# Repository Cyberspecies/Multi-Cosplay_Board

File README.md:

# Multi-Cosplay_Board
The board should be capable of driving nearly any electrically active cosplay suit or project including props. The system must also remain cheap and affordable with inter and extrapolation capabilities allowing it to be reducibly complex and still function. The software must also be easy to configure and implement (as this is a platform supported by [ARCOS](https://github.com/XCR1793/ARCOS)).

## Features
* Movement detection via the [ICM-20948](https://invensense.tdk.com/products/motion-tracking/9-axis/icm-20948/), which allows users to track their linear and angular accelerations for animations that require shaking, turning or any other activity requiring user displacement.
* Designed with a small form-factor which users can take advantage of by hiding the circuit board in tight spaces to not get it in the way of aesthetics.
* Fast processing core being the [ESP32-S3 Modules](https://www.espressif.com/en/products/socs/esp32) contains a 280Mhz dual core processor allowing partial asynchronous parallel calculations required for detecting user input and computing sequences at the same time whilst remaining as affordable as possible.

## Roadmap
* Milestone: Nothing Yet
* Work In Progress: Ideation & PCB Component Placement & Feature Integration
* Planned: MCB Version 1
* Planned: ARCOS Integration

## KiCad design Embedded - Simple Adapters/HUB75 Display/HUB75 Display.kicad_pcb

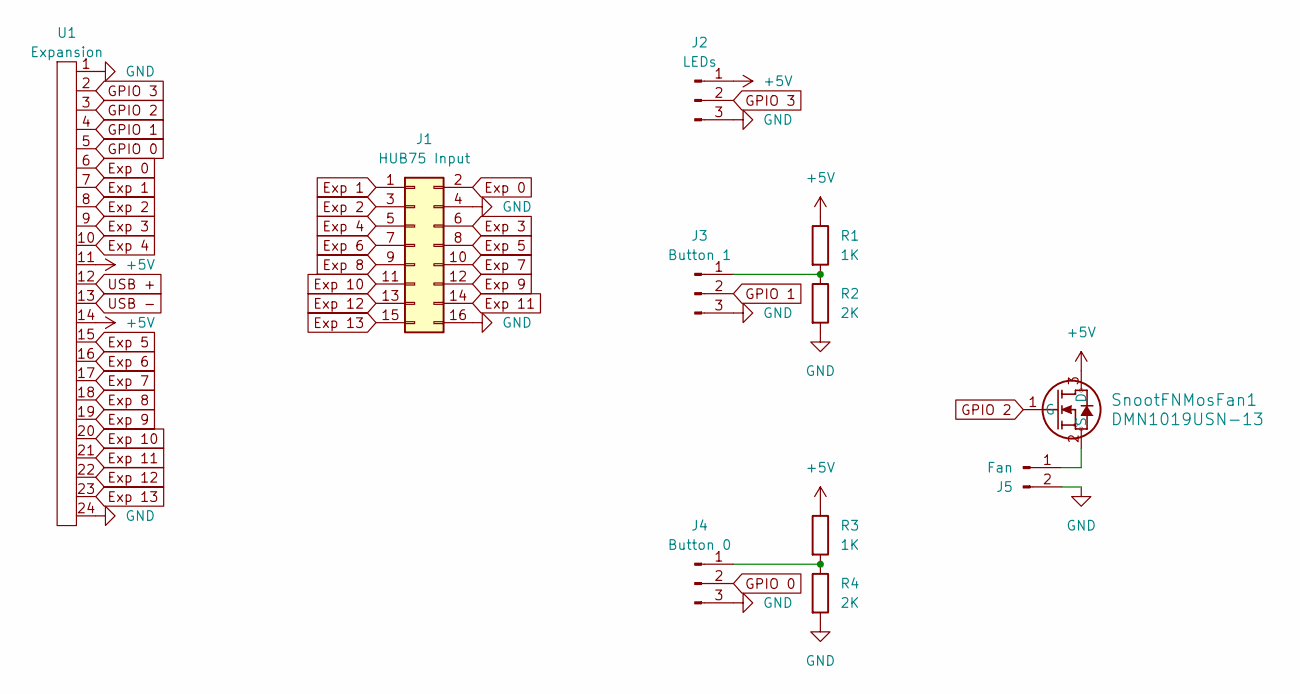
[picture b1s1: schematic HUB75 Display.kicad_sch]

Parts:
J1: HUB75 Input; PinHeader_2x08_P2.54mm_Vertical
J2: LEDs; PinHeader_1x03_P2.54mm_Vertical
J3: Button 1; PinHeader_1x03_P2.54mm_Vertical
J4: Button 0; PinHeader_1x03_P2.54mm_Vertical
J5: Fan; PinHeader_1x02_P2.54mm_Vertical
R1, R3: 1K; R_0603_1608Metric_Pad0.98x0.95mm_HandSolder
R2, R4: 2K; R_0603_1608Metric_Pad0.98x0.95mm_HandSolder
SnootFNMosFan1: DMN1019USN-13; SOT-23-3
U1: Expansion; FFC Aliexpress 0.5mm 24P

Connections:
+5V: J2.1, R1.1, R3.1, SnootFNMosFan1.3 (D), U1.11, U1.14
Exp 0: J1.2, U1.6
Exp 1: J1.1, U1.7
Exp 2: J1.3, U1.8
Exp 3: J1.6, U1.9
Exp 4: J1.5, U1.10
Exp 5: J1.8, U1.15
Exp 6: J1.7, U1.16
Exp 7: J1.10, U1.17
Exp 8: J1.9, U1.18
Exp 9: J1.12, U1.19
Exp 10: J1.11, U1.20
Exp 11: J1.14, U1.21
Exp 12: J1.13, U1.22
Exp 13: J1.15, U1.23
GND: J1.4, J1.16, J2.3, J3.3, J4.3, J5.2, R2.2, R4.2, U1.1, U1.24
GPIO 0: J4.2, U1.5
GPIO 1: J3.2, U1.4
GPIO 2: SnootFNMosFan1.1 (G), U1.3
GPIO 3: J2.2, U1.2
unnamed: J3.1, R1.2, R2.1
unnamed: J4.1, R3.2, R4.1
unnamed: J5.1, SnootFNMosFan1.2 (S)
USB +: U1.12
USB -: U1.13

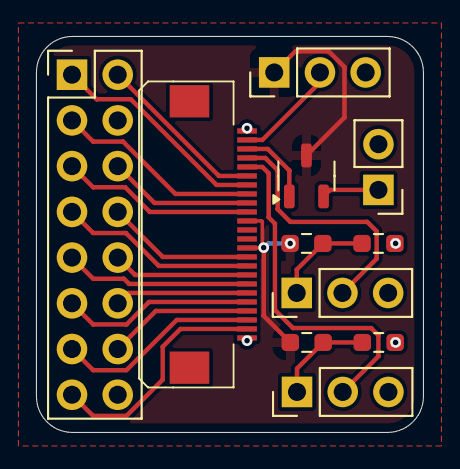
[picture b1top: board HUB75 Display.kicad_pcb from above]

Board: 2 copper layers, 21.5 x 22.0 mm, 11 parts (0 on the bottom side), 23 nets.

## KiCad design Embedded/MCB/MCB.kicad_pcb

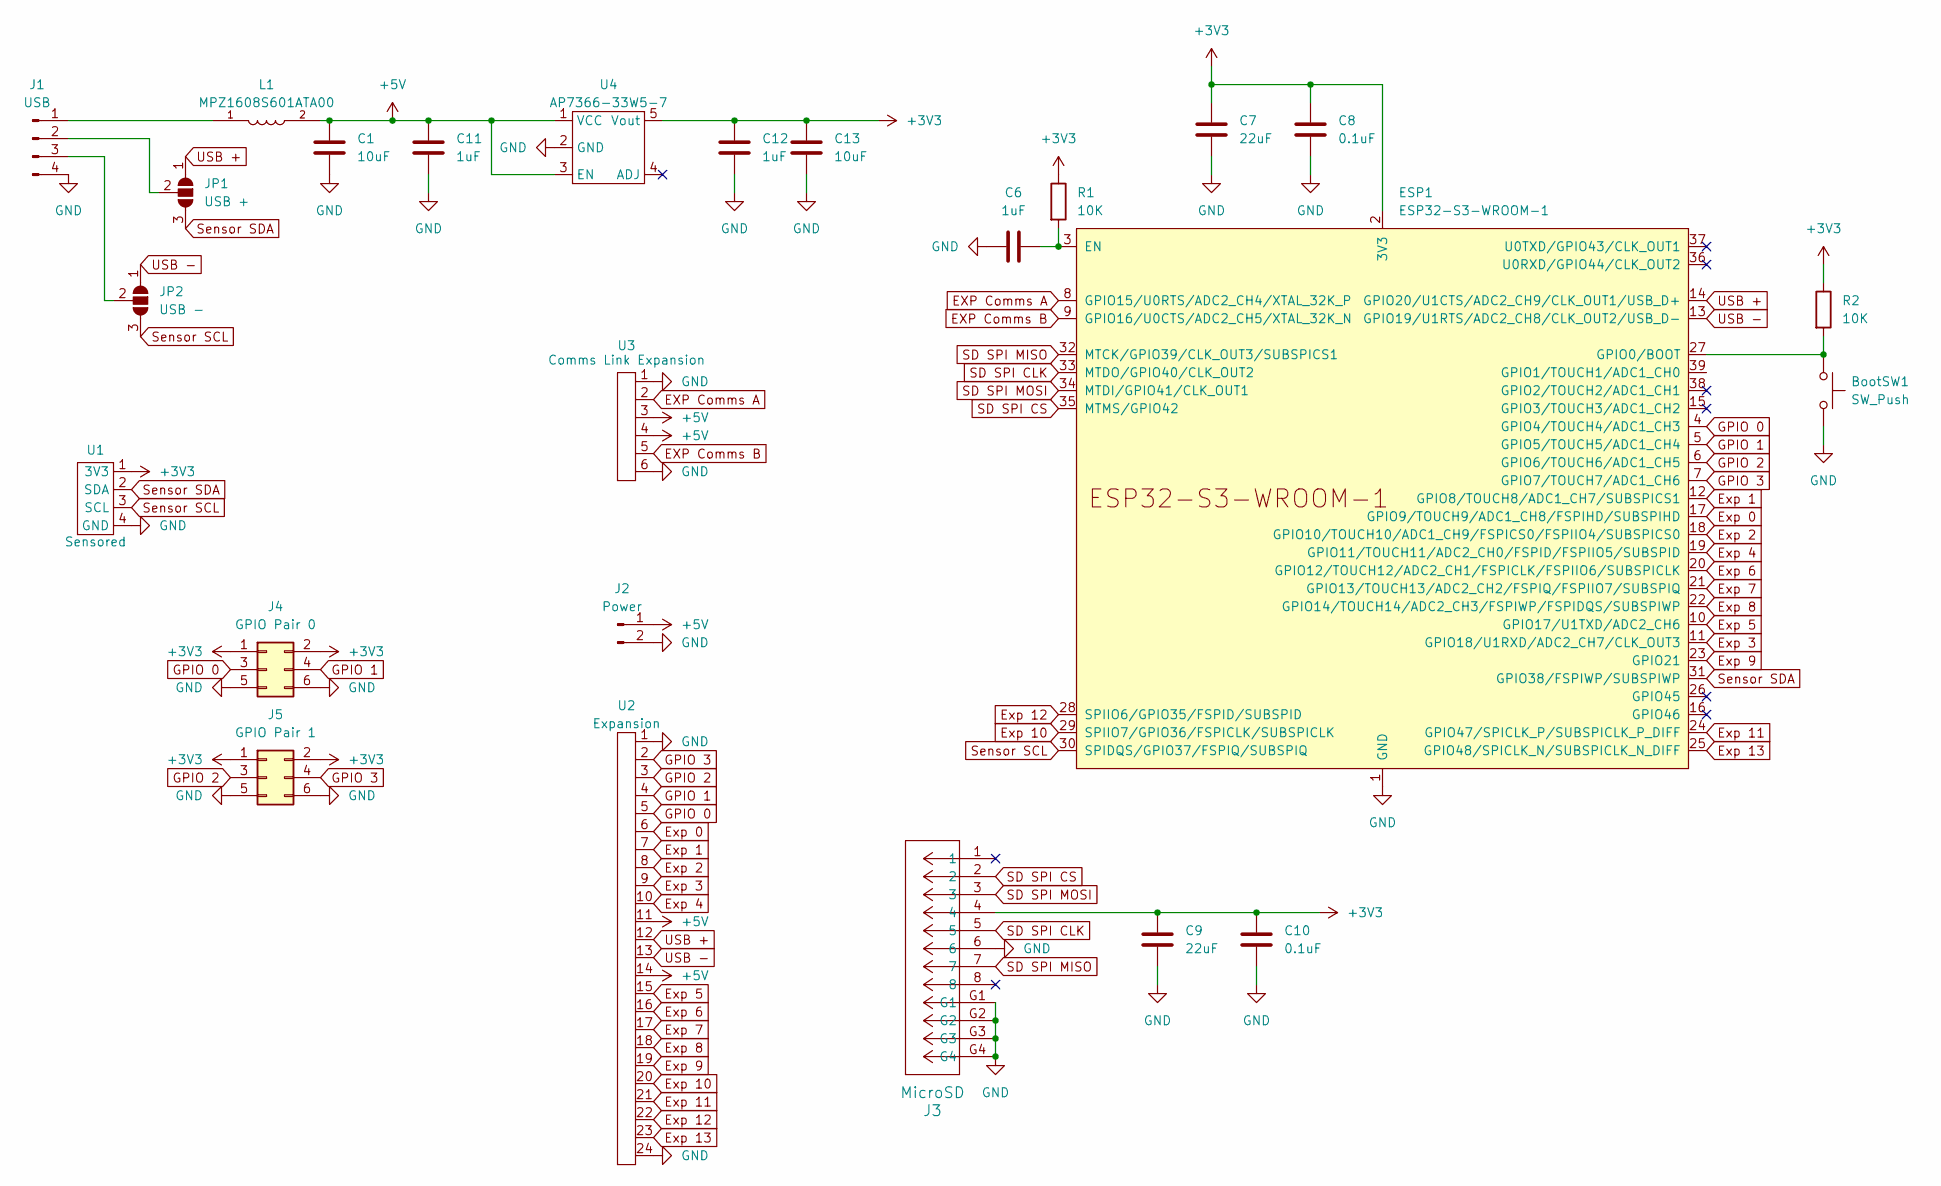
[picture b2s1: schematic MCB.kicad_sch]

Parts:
BootSW1: SW_Push; Button-R-667843
C1, C13: 10uF; C_0603_1608Metric
C6: 1uF; C_0603_1608Metric
C7, C9: 22uF; C_0603_1608Metric_Pad1.08x0.95mm_HandSolder
C8, C10: 0.1uF; C_0603_1608Metric_Pad1.08x0.95mm_HandSolder
C11, C12: 1uF; R_0603_1608Metric
ESP1: ESP32-S3-WROOM-1; ESP32-S3-WROOM-1U
J1: USB; Hirose_DF13-04P-1.25DS_1x04_P1.25mm_Horizontal
J2: Power; Hirose_DF13-02P-1.25DS_1x02_P1.25mm_Horizontal
J3: MicroSD; CONN12_47309-2651_MOL
J4: GPIO Pair 0; PinHeader_2x03_P2.54mm_Vertical
J5: GPIO Pair 1; PinHeader_2x03_P2.54mm_Vertical
JP1: USB +; SolderJumper-3_P1.3mm_Open_RoundedPad1.0x1.5mm
JP2: USB -; SolderJumper-3_P1.3mm_Open_RoundedPad1.0x1.5mm
L1: MPZ1608S601ATA00; INDC1608X95N
R1, R2: 10K; R_0603_1608Metric
U1: Sensored
U2: Expansion; FFC Aliexpress 0.5mm 24P
U3: Comms Link Expansion; FFC Aliexpress 0.5mm 6P
U4: AP7366-33W5-7; AP7366

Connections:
+3V3: C7.1, C8.1, C9.1, C10.1, C12.1, C13.1, ESP1.2 (3V3), J3.4, J4.1, J4.2, J5.1, J5.2, R1.1, R2.1, U1.1 (3V3), U4.5 (Vout)
+5V: C1.1, C11.1, J2.1, L1.2, U2.11, U2.14, U3.3, U3.4, U4.1 (VCC), U4.3 (EN)
EXP Comms A: ESP1.8 (GPIO15/U0RTS/ADC2_CH4/XTAL_32K_P), U3.2
EXP Comms B: ESP1.9 (GPIO16/U0CTS/ADC2_CH5/XTAL_32K_N), U3.5
Exp 0: ESP1.17 (GPIO9/TOUCH9/ADC1_CH8/FSPIHD/SUBSPIHD), U2.6
Exp 1: ESP1.12 (GPIO8/TOUCH8/ADC1_CH7/SUBSPICS1), U2.7
Exp 2: ESP1.18 (GPIO10/TOUCH10/ADC1_CH9/FSPICS0/FSPIIO4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), U2.8
Exp 3: ESP1.11 (GPIO18/U1RXD/ADC2_CH7/CLK_OUT3), U2.9
Exp 4: ESP1.19 (GPIO11/TOUCH11/ADC2_CH0/FSPID/FSPIIO5/S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), U2.10
Exp 5: ESP1.10 (GPIO17/U1TXD/ADC2_CH6), U2.15
Exp 6: ESP1.20 (GPIO12/TOUCH12/ADC2_CH1/FSPICLK/FSPIIO6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), U2.16
Exp 7: ESP1.21 (GPIO13/TOUCH13/ADC2_CH2/FSPIQ/FSPIIO7/S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), U2.17
Exp 8: ESP1.22 (GPIO14/TOUCH14/ADC2_CH3/FSPIWP/FSPIDQS/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), U2.18
Exp 9: ESP1.23 (GPIO21), U2.19
Exp 10: ESP1.29 (SPIIO7/GPIO36/FSPICLK/SUBSPICLK), U2.20
Exp 11: ESP1.24 (GPIO47/SPICLK_P/SUBSPICLK_P_DIFF), U2.21
Exp 12: ESP1.28 (SPIIO6/GPIO35/FSPID/SUBSPID), U2.22
Exp 13: ESP1.25 (GPIO48/SPICLK_N/SUBSPICLK_N_DIFF), U2.23
GND: BootSW1.2, C1.2, C6.1, C7.2, C8.2, C9.2, C10.2, C11.2, C12.2, C13.2, ESP1.1 (GND), ESP1.40 (GND), ESP1.41 (GND), J1.4, J2.2, J3.6, J3.G1, J3.G2, J3.G3, J3.G4, J4.5, J4.6, J5.5, J5.6, U1.4 (GND), U2.1, U2.24, U3.1, U3.6, U4.2 (GND)
GPIO 0: ESP1.4 (GPIO4/TOUCH4/ADC1_CH3), J4.3, U2.5
GPIO 1: ESP1.5 (GPIO5/TOUCH5/ADC1_CH4), J4.4, U2.4
GPIO 2: ESP1.6 (GPIO6/TOUCH6/ADC1_CH5), J5.3, U2.3
GPIO 3: ESP1.7 (GPIO7/TOUCH7/ADC1_CH6), J5.4, U2.2
unnamed: C6.2, ESP1.3 (EN), R1.2
unnamed: BootSW1.1, ESP1.27 (GPIO0/BOOT), R2.2
unnamed: J1.1, L1.1
unnamed: J1.2, JP1.2 (C)
unnamed: J1.3, JP2.2 (C)
SD SPI CLK: ESP1.33 (MTDO/GPIO40/CLK_OUT2), J3.5
SD SPI CS: ESP1.35 (MTMS/GPIO42), J3.2
SD SPI MISO: ESP1.32 (MTCK/GPIO39/CLK_OUT3/SUBSPICS1), J3.7
SD SPI MOSI: ESP1.34 (MTDI/GPIO41/CLK_OUT1), J3.3
Sensor SCL: ESP1.30 (SPIDQS/GPIO37/FSPIQ/SUBSPIQ), JP2.3 (B), U1.3 (SCL)
Sensor SDA: ESP1.31 (GPIO38/FSPIWP/SUBSPIWP), JP1.3 (B), U1.2 (SDA)
USB +: ESP1.14 (GPIO20/U1CTS/ADC2_CH9/CLK_OUT1/USB_D+), JP1.1 (A), U2.12
USB -: ESP1.13 (GPIO19/U1RTS/ADC2_CH8/CLK_OUT2/USB_D-), JP2.1 (A), U2.13

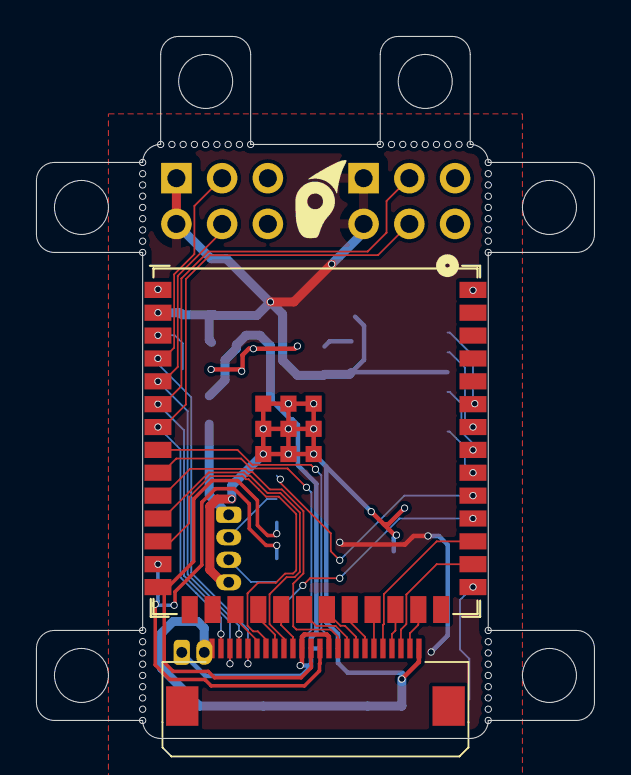
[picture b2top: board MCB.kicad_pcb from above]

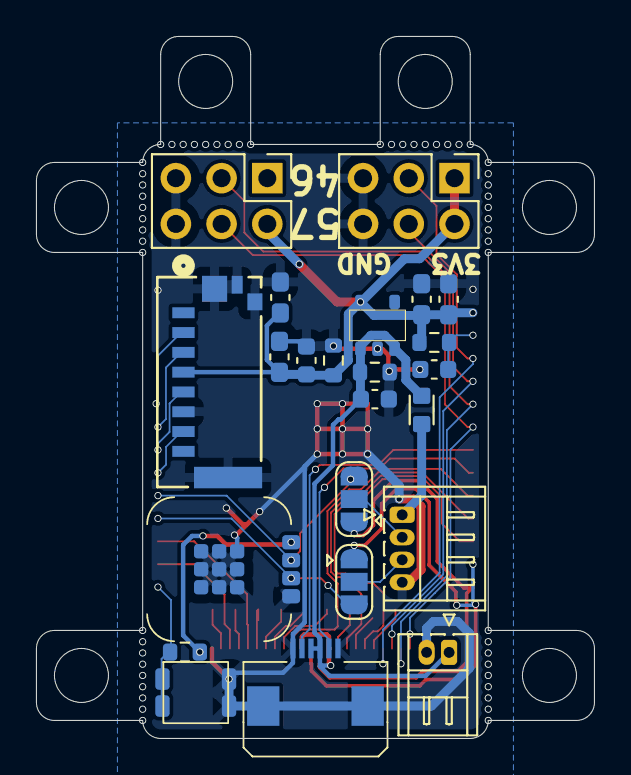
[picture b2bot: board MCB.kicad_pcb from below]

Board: 2 copper layers, 31.0 x 39.0 mm, 25 parts (23 on the bottom side), 36 nets.

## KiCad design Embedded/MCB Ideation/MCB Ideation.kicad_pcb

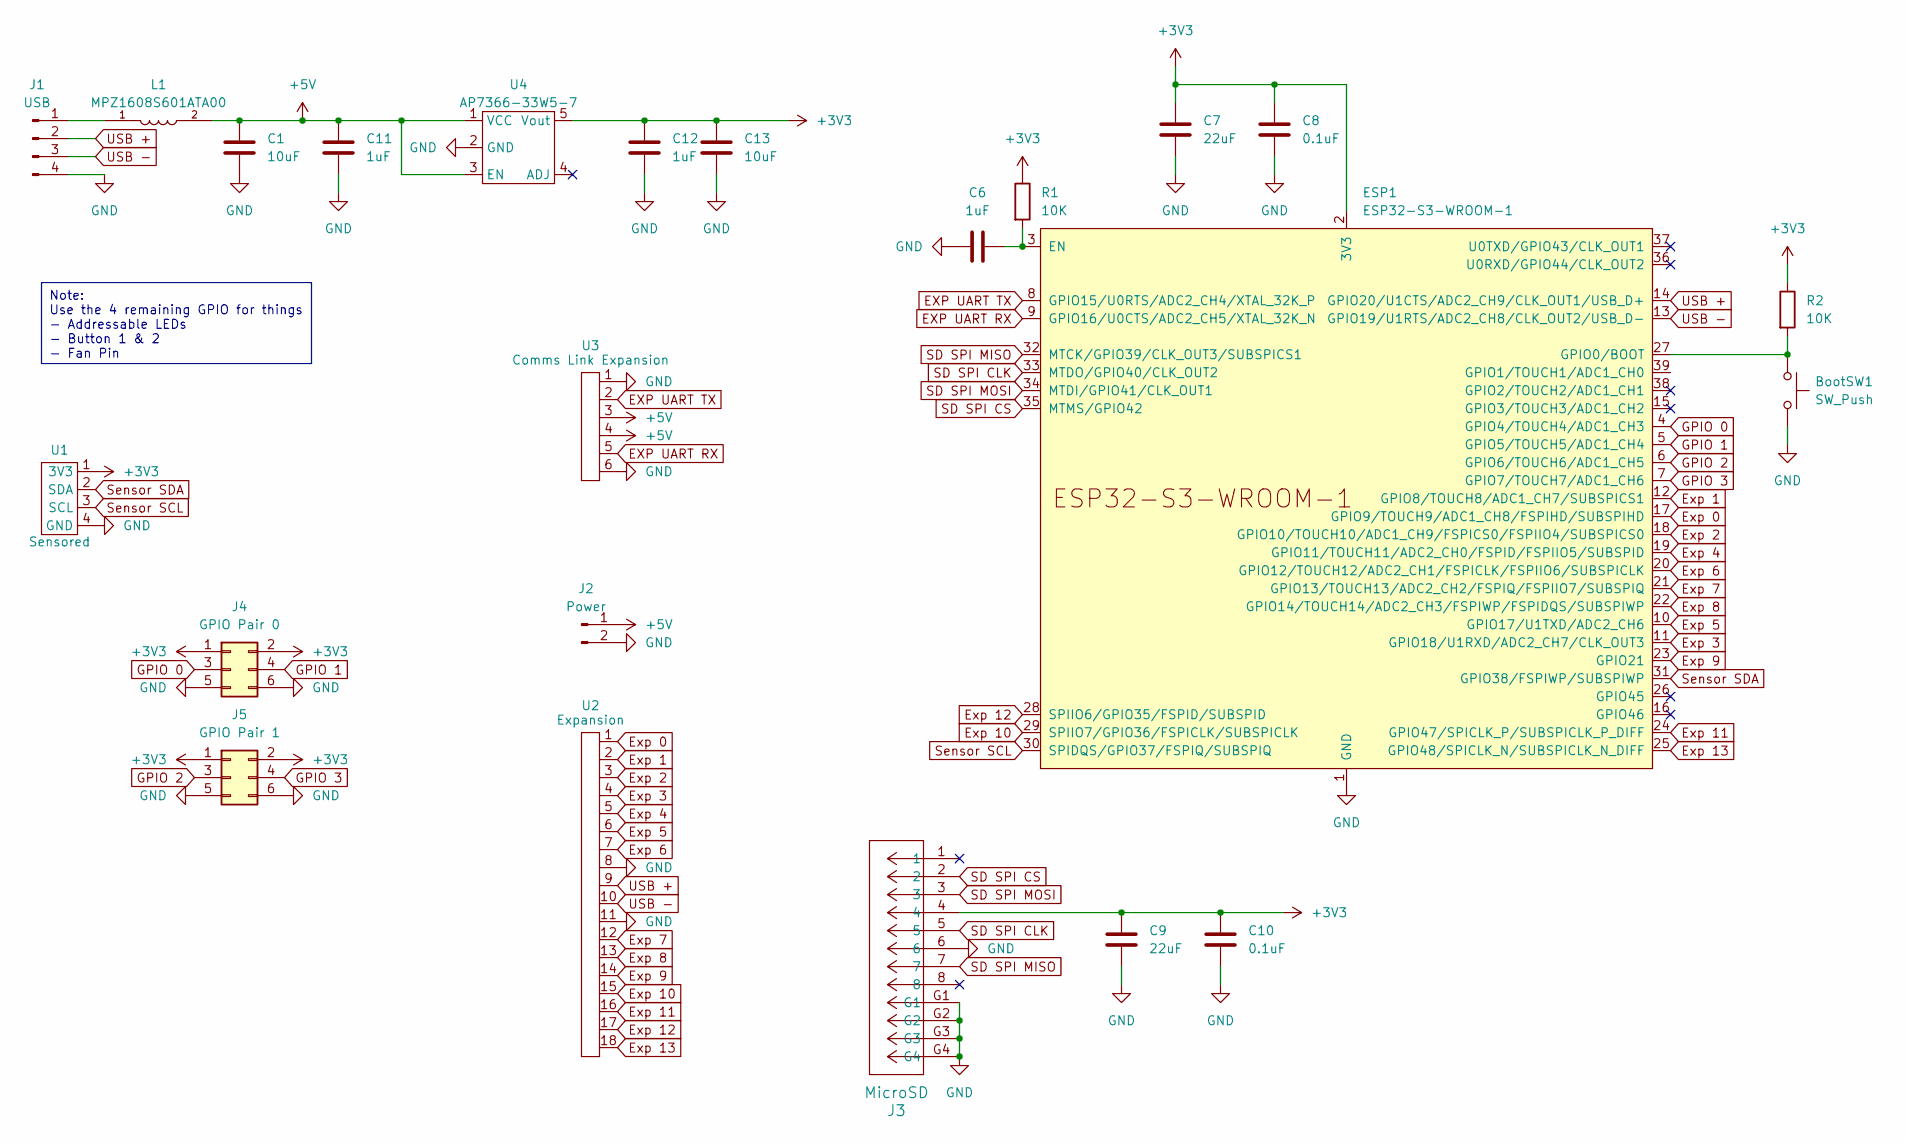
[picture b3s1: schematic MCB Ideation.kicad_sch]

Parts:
BootSW1: SW_Push; Button-R-667843
C1, C13: 10uF; C_0603_1608Metric
C6: 1uF; C_0603_1608Metric
C7, C9: 22uF; C_0603_1608Metric_Pad1.08x0.95mm_HandSolder
C8: 0.1uF; C_0603_1608Metric_Pad1.08x0.95mm_HandSolder
C10: 0.1uF; C_0402_1005Metric_Pad0.74x0.62mm_HandSolder
C11, C12: 1uF; R_0603_1608Metric
ESP1: ESP32-S3-WROOM-1; ESP32-S3-WROOM-1U
J1: USB; Hirose_DF13-04P-1.25DS_1x04_P1.25mm_Horizontal
J2: Power; Hirose_DF13-02P-1.25DS_1x02_P1.25mm_Horizontal
J3: MicroSD; CONN12_47309-2651_MOL
J4: GPIO Pair 0; PinHeader_2x03_P2.54mm_Vertical
J5: GPIO Pair 1; PinHeader_2x03_P2.54mm_Vertical
L1: MPZ1608S601ATA00; INDC1608X95N
R1, R2: 10K; R_0603_1608Metric
U1: Sensored
U2: Expansion; FFC Aliexpress 0.5mm 18P
U3: Comms Link Expansion; FFC Aliexpress 0.5mm 6P
U4: AP7366-33W5-7; AP7366

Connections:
+3V3: C7.1, C8.1, C9.1, C10.1, C12.1, C13.1, ESP1.2 (3V3), J3.4, J4.1, J4.2, J5.1, J5.2, R1.1, R2.1, U1.1 (3V3), U4.5 (Vout)
+5V: C1.1, C11.1, J2.1, L1.2, U3.3, U3.4, U4.1 (VCC), U4.3 (EN)
EXP UART RX: ESP1.9 (GPIO16/U0CTS/ADC2_CH5/XTAL_32K_N), U3.5
EXP UART TX: ESP1.8 (GPIO15/U0RTS/ADC2_CH4/XTAL_32K_P), U3.2
Exp 0: ESP1.17 (GPIO9/TOUCH9/ADC1_CH8/FSPIHD/SUBSPIHD), U2.1
Exp 1: ESP1.12 (GPIO8/TOUCH8/ADC1_CH7/SUBSPICS1), U2.2
Exp 2: ESP1.18 (GPIO10/TOUCH10/ADC1_CH9/FSPICS0/FSPIIO4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), U2.3
Exp 3: ESP1.11 (GPIO18/U1RXD/ADC2_CH7/CLK_OUT3), U2.4
Exp 4: ESP1.19 (GPIO11/TOUCH11/ADC2_CH0/FSPID/FSPIIO5/S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), U2.5
Exp 5: ESP1.10 (GPIO17/U1TXD/ADC2_CH6), U2.6
Exp 6: ESP1.20 (GPIO12/TOUCH12/ADC2_CH1/FSPICLK/FSPIIO6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), U2.7
Exp 7: ESP1.21 (GPIO13/TOUCH13/ADC2_CH2/FSPIQ/FSPIIO7/S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), U2.12
Exp 8: ESP1.22 (GPIO14/TOUCH14/ADC2_CH3/FSPIWP/FSPIDQS/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), U2.13
Exp 9: ESP1.23 (GPIO21), U2.14
Exp 10: ESP1.29 (SPIIO7/GPIO36/FSPICLK/SUBSPICLK), U2.15
Exp 11: ESP1.24 (GPIO47/SPICLK_P/SUBSPICLK_P_DIFF), U2.16
Exp 12: ESP1.28 (SPIIO6/GPIO35/FSPID/SUBSPID), U2.17
Exp 13: ESP1.25 (GPIO48/SPICLK_N/SUBSPICLK_N_DIFF), U2.18
GND: BootSW1.2, C1.2, C6.1, C7.2, C8.2, C9.2, C10.2, C11.2, C12.2, C13.2, ESP1.1 (GND), ESP1.40 (GND), ESP1.41 (GND), J1.4, J2.2, J3.6, J3.G1, J3.G2, J3.G3, J3.G4, J4.5, J4.6, J5.5, J5.6, U1.4 (GND), U2.8, U2.11, U3.1, U3.6, U4.2 (GND)
GPIO 0: ESP1.4 (GPIO4/TOUCH4/ADC1_CH3), J4.3
GPIO 1: ESP1.5 (GPIO5/TOUCH5/ADC1_CH4), J4.4
GPIO 2: ESP1.6 (GPIO6/TOUCH6/ADC1_CH5), J5.3
GPIO 3: ESP1.7 (GPIO7/TOUCH7/ADC1_CH6), J5.4
unnamed: C6.2, ESP1.3 (EN), R1.2
unnamed: BootSW1.1, ESP1.27 (GPIO0/BOOT), R2.2
unnamed: J1.1, L1.1
SD SPI CLK: ESP1.33 (MTDO/GPIO40/CLK_OUT2), J3.5
SD SPI CS: ESP1.35 (MTMS/GPIO42), J3.2
SD SPI MISO: ESP1.32 (MTCK/GPIO39/CLK_OUT3/SUBSPICS1), J3.7
SD SPI MOSI: ESP1.34 (MTDI/GPIO41/CLK_OUT1), J3.3
Sensor SCL: ESP1.30 (SPIDQS/GPIO37/FSPIQ/SUBSPIQ), U1.3 (SCL)
Sensor SDA: ESP1.31 (GPIO38/FSPIWP/SUBSPIWP), U1.2 (SDA)
USB +: ESP1.14 (GPIO20/U1CTS/ADC2_CH9/CLK_OUT1/USB_D+), J1.2, U2.9
USB -: ESP1.13 (GPIO19/U1RTS/ADC2_CH8/CLK_OUT2/USB_D-), J1.3, U2.10

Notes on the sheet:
Note: Use the 4 remaining GPIO for things - Addressable LEDs - Button 1 & 2 - Fan Pin

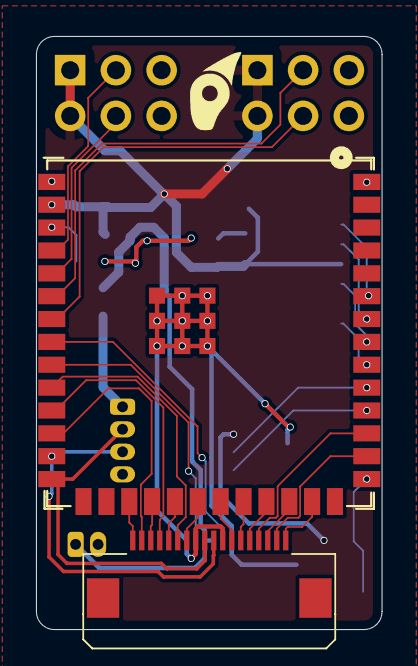
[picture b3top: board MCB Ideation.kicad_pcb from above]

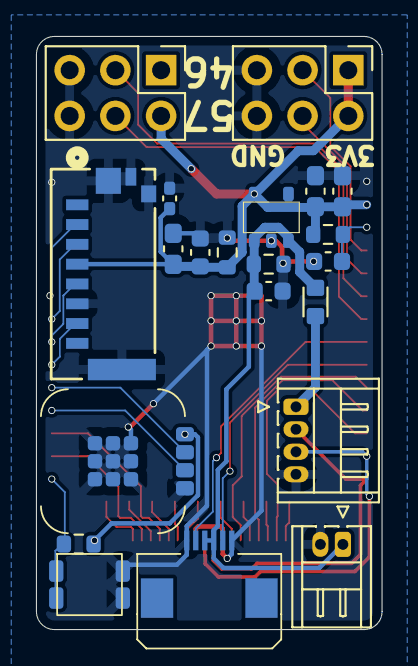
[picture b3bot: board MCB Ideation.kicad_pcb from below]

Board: 2 copper layers, 19.2 x 33.0 mm, 23 parts (21 on the bottom side), 34 nets.

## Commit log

2024-12-15 Ideation of PCB Layout and Function
2024-12-15 Ideation PCB Component Compaction
2024-12-16 Feature Listing & Organisation
2024-12-16 Fixed Broken 3D Models
2024-12-24 Added Sensored
2024-12-24 Added Expansion Pins
2024-12-24 Added USB Connectivity & Verified Expansion Pins
2024-12-24 Added Secondary Expansion (Comms Link)
2024-12-25 Added USB and Power Ports
2024-12-25 Rerouted Some Components
2024-12-25 Added GPIO Pins
2024-12-25 Modified GPIO Expansion Pins
2024-12-26 Added Substructure Adapter & Extended MCB Expansion Pins
2024-12-26 Added USB-2WComms Solder Bridge
2024-12-26 Modified Some Traces for Lower Noise
2024-12-26 Migrated Substructure
    The substructure KiCAD files were migrated to another repo as it was directly part of the MCB
2024-12-26 Modified Diagram to match project scope
2024-12-31 Added Combined Fabrication Files for (MCB, Substructure, Display, UI and HUB75)
2025-03-07 Added Cern OHL V2 License
2025-07-29 Added New project scope and purpose
2025-07-29 Added Compatible Firmwares/Libraries
